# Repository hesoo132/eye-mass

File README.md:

# Eye-Mass Board  

## 🔎 Overview
**Eye-Mass** is a custom embedded hardware board designed for **real-time image processing and AI experimentation**.  
It integrates a camera (OV5640), external SDRAM, motor control, and communication interfaces to enable tasks such as **capturing and analyzing images of components inside a box**.

---

## 🔧 Hardware Features

| Component               | Purpose                                                                 |
|-------------------------|-------------------------------------------------------------------------|
| **Debug LED**           | Visual feedback for board status and firmware debugging                 |
| **SDRAM**               | Additional memory for buffering image data and running lightweight AI   |
| **OV5640 Camera**       | Captures images (e.g., counting SMD components inside a box)            |
| **Motor Driver**        | Moves the camera to capture the entire box view                         |
| **FDCAN**               | High-speed, reliable communication with external modules                |
| **USART**               | Serial interface for debugging and logging                              |
| **Temperature Sensor**  | Monitors motor driver and board ambient temperature                     |
| **Current/Voltage Monitor** | Measures system power consumption and provides protection           |

---

## 📸 Hardware Overview
| PCB Top | PCB Bottom |
|---------|------------|
|  |  |

---

## ✅ Current Status
- [x] Schematic design completed
- [x] PCB prototype (Rev. A) fabricated
- [x] SDRAM bring-up and validation
- [ ] Camera interface bring-up (OV5640)
- [x] Motor control & positioning test
- [x] Communication test (FDCAN, USART)
- [ ] Firmware integration (image capture + AI experimentation)

---

## 📑 References
- [STM32H7 Reference Manual](https://www.st.com/resource/en/reference_manual/dm00314099.pdf)  
- [OV5640 Camera Datasheet](https://www.arducam.com/downloads/datasheet/OV5640DS.pdf)

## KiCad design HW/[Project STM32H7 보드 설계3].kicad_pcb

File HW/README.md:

# Eye-Mass Hardware Design

## 🔎 Overview
The **Eye-Mass Board** is a custom embedded platform designed for **camera-based vision tasks and AI experimentation**.  
It integrates an OV5640 camera, external SDRAM, motor driver, and multiple debug/monitoring features.

---

## 📸 PCB Overview
| Top View | Bottom View |
|----------|-------------|
|  |  |

---

## 📑 Design Resources

- **Schematics**: [eye-mass.pdf](eye-mass.pdf) (PDF for quick view)
    
---

## 🔧 Key Hardware Notes
- **EDA Tool**: KiCad 9.0  
- **PCB Stackup**: 6-layer, impedance-controlled for high-speed (DCMI, FDCAN)  
- **Memory**: External SDRAM for real-time image buffering + AI workloads  
- **Camera**: OV5640 with DCMI interface for capturing and analysis  
- **Motor Driver**: Enables camera positioning to capture full target area  
- **Debugging**: LEDs + USART interface  
- **Monitoring**: Temperature and current/voltage sensing  

---

## 🧩 Schematic Highlights

### 1) MCU — STM32H723ZGT6

- **Device**: STM32H723ZGT6 
- **Connections**: Debug UART, **ST-Link Mini** (SWD), boot-mode pins, GPIO banks **PA/PB/PC/PD/PE/PF/PG**, external clock **TCXO 12 MHz**, reset circuit  
- **Purpose**: Central control with dedicated debug/boot paths and ample I/O for peripherals

### 2) SDRAM — IS42S16320F-7BL

- **Device**: IS42S16320F-7BL  
- **Interface**: **FMC** — DQ0–DQ15, A0–A12, BA0–BA1, **SDNWE/SDNCAS/SDNRAS/SDNE0/SDCKE0/SDCLK**, NBL0/NBL1  
- **Purpose**: External memory to expand capacity for image buffering and lightweight AI execution

### 3) Power

- **Key ICs**: **INA219BxD** (current/voltage monitor), **TPS562201** (buck converter)  
- **Rails**: From **+12 V** input to **+5 V / +3.3 V / +2.8 V / +1.8 V**  
- **Purpose**: Stable multi-rail supply with inline power telemetry for easier power management

### 4) Camera — OV5640

- **Sensor**: **OV5640**  
- **Interface**: **DCMI** (D0–D7, HSYNC, VSYNC, PIXCLK) + **I²C4** (SCL, SDA)  
- **Power & Control**: **+1.8 V / +2.8 V / +3.3 V** rails, LED control (**Camera_LED**, **FLASH**, **FLASH_PWM**)  
- **Use Case**: Capturing images for tasks like **counting SMD components inside a box**

### 5) FDCAN

- **Transceiver**: **MCP2562FD**  
- **Connections**: MCU **FDCAN_Tx3 / FDCAN_Rx3** ↔ bus **CANH/CANL**; includes **120 Ω** termination  
- **Purpose**: Robust CAN communication to external modules/systems

### 6) Temperature — AS6221 ×2

- **Sensors**: **AS6221** ×2  
- **Interface**: **I²C2** (SCL, SDA)  
- **Purpose**: Dual-point temperature monitoring (e.g., motor driver and board ambient)

### 7) Motor Driver — A4988

- **Driver**: **A4988**  
- **Signals**: **STEP, DIR, ENABLE, MS1, MS2, MS3**; outputs **1A/1B/2A/2B**  
- **Purpose**: Stepper control with microstepping configuration for camera positioning

### 8) microSD — SDMMC2

- **Interface**: **SDMMC2** — D0–D3, CMD, CLK, INT  
- **Purpose**: Removable storage for images and logs

---

## ✅ Progress
- [x] Schematics completed  
- [x] PCB prototype (Rev. A) fabricated  
- [x] SDRAM bring-up (partial validation ongoing)  
- [ ] Camera interface bring-up (OV5640)  
- [x] Motor driver test & positioning control  
- [x] Communication tests (FDCAN / USART)

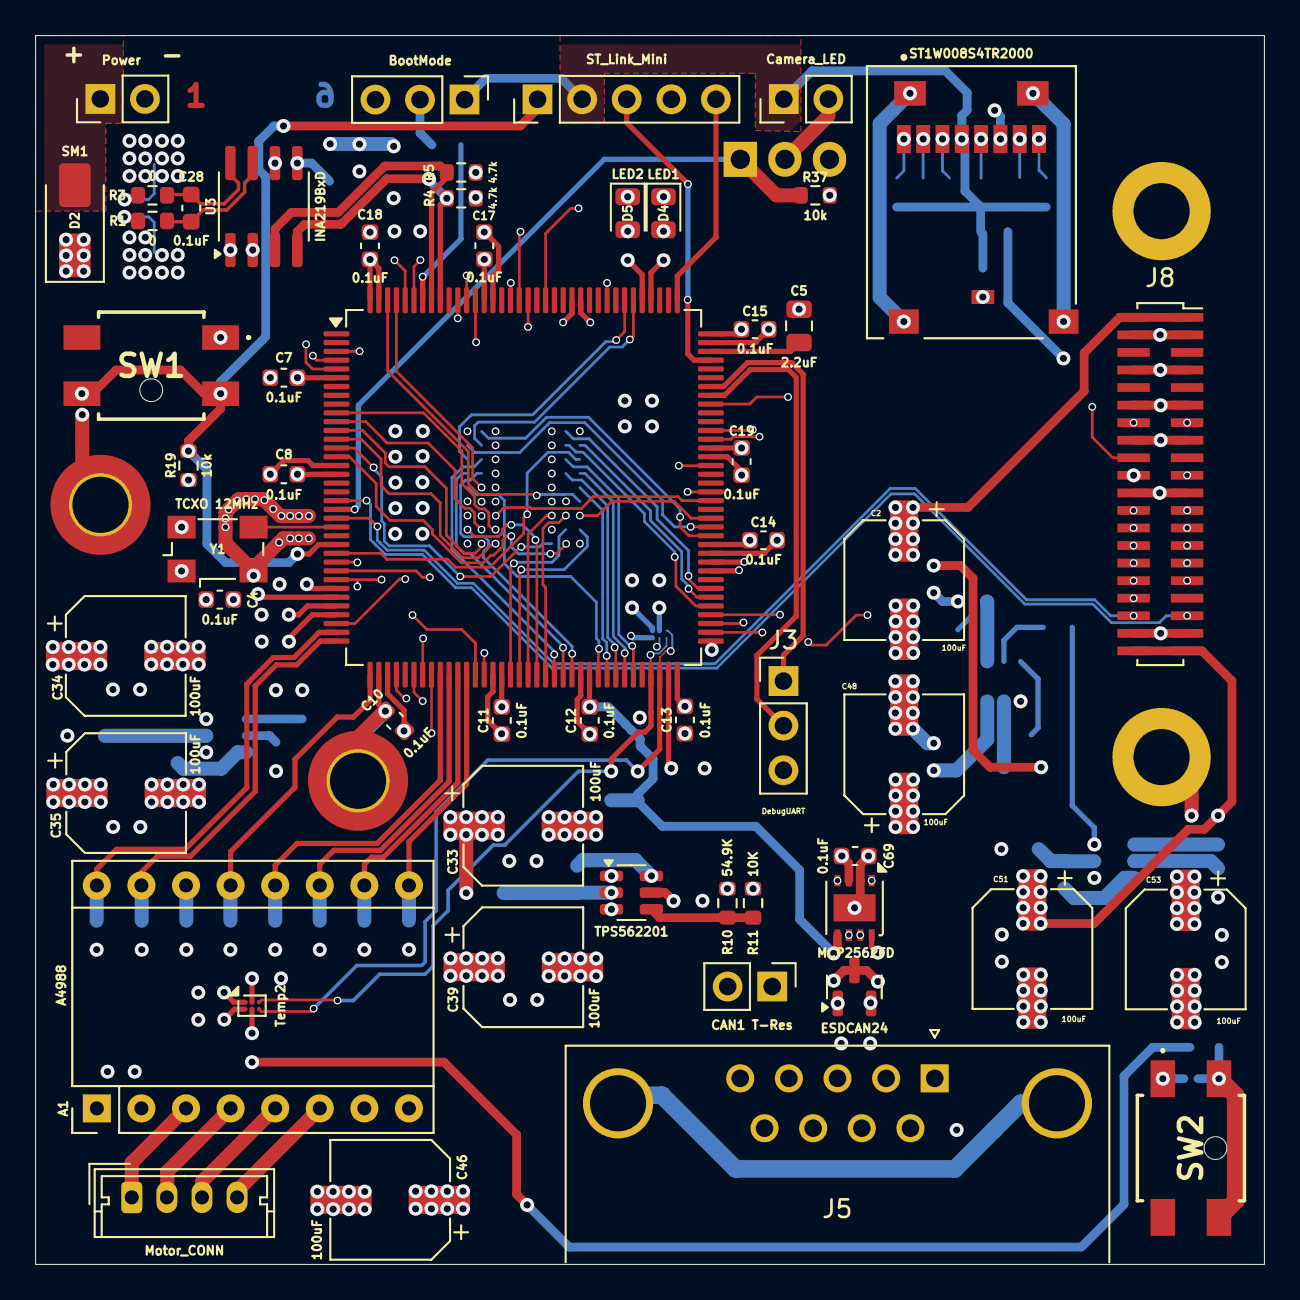
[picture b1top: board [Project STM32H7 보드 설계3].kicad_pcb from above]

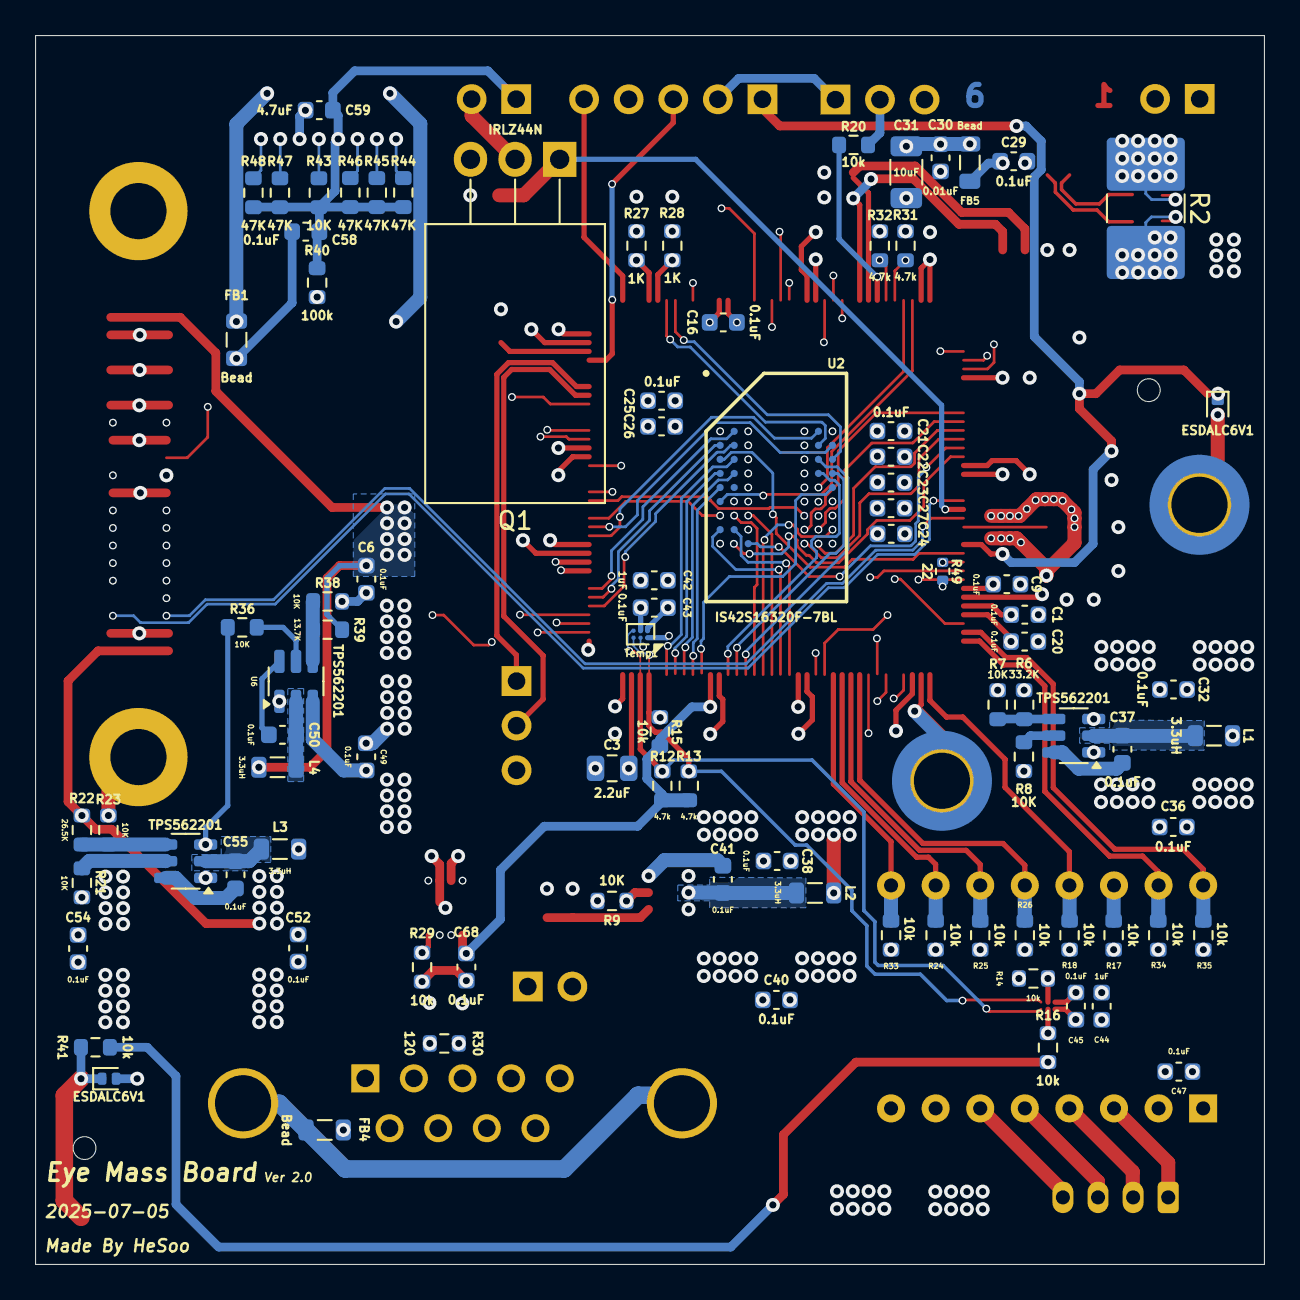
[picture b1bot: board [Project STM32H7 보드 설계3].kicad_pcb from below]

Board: 6 copper layers, 70.0 x 70.0 mm, 147 parts (90 on the bottom side), 135 nets.

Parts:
A1: A4988; Pololu_Breakout-16_15.2x20.3mm
C1, C4, C6, C7, C8, C9, C10, C11, C12, C13, C14, C15, C16, C17, C18, C19, C20, C21, C22, C23, C24, C25, C26, C27, C28, C29, C32, C36, C37, C38, C40, C41, C43, C45, C47, C49, C50, C52, C54, C55, C58, C68, C69: 0.1uF; C_0603_1608Metric
C2, C33, C34, C35, C39, C46, C48, C51, C53: 100uF; CP_Elec_6.3x5.9
C3, C5: 2.2uF; C_0805_2012Metric
C30: 0.01uF; C_0603_1608Metric
C31: 10uF; C_1206_3216Metric
C42, C44: 1uF; C_0603_1608Metric
C59: 4.7uF; C_0603_1608Metric
D1: ESDCAN24; SOT-23
D2: SM1; D_SMA
D3, D6: ESDALC6V1; D_SOD-882D
D4: LED1; LED_0805_2012Metric
D5: LED2; LED_0805_2012Metric
FB1, FB4, FB5: Bead; L_0805_2012Metric
H1, H2: MountingHole_Pad; MountingHole_3.2mm_M3_DIN965_Pad
J1: Power; PinHeader_1x02_P2.54mm_Vertical
J2: ST_Link_Mini; PinHeader_1x05_P2.54mm_Vertical
J3: DebugUART; PinHeader_1x03_P2.54mm_Vertical
J4: CAN1 T-Res; PinHeader_1x02_P2.54mm_Vertical
J5: FDCAN_1; DSUB-9_Female_Horizontal_P2.77x2.84mm_EdgePinOffset7.70mm_H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
J6: BootMode; PinHeader_1x03_P2.54mm_Vertical
J7: Camera_LED; PinHeader_1x02_P2.54mm_Vertical
J8: OV5640; PinSocket_2x20_P1.00mm_Vertical_SMD
J9: Motor_CONN; Molex_Micro-Latch_53253-0470_1x04_P2.00mm_Vertical
J10: ST1W008S4TR2000; JAE_ST1W008S4TR2000
L1, L2, L3, L4: 3.3uH; L_0805_2012Metric
Q1: IRLZ44N; TO-220-3_Horizontal_TabDown
R1, R3: 0; R_0603_1608Metric
R2: 0.1; R_2816_7142Metric
R4, R5, R12, R13, R31, R32: 4.7k; R_0603_1608Metric
R6: 33.2K; R_0603_1608Metric
R7, R8, R9, R11, R21, R23, R36, R38, R43: 10K; R_0603_1608Metric
R10: 54.9K; R_0603_1608Metric
R14, R15, R16, R17, R18, R19, R20, R24, R25, R26, R29, R33, R34, R35, R37, R41: 10k; R_0603_1608Metric
R22: 26.5K; R_0603_1608Metric
R27, R28: 1K; R_0603_1608Metric
R30: 120; R_0603_1608Metric
R39: 13.7K; R_0603_1608Metric
R40: 100k; R_0603_1608Metric
R44, R45, R46, R47, R48: 47K; R_0603_1608Metric
R49: 22; R_0402_1005Metric
SW1, SW2: RESET; TLSMDT3C020GLFS
Temp1, Temp2: AS6221; WLCSP-6_1.4x1.0mm_P0.4mm
U1: STM32H723ZGTx; LQFP-144_20x20mm_P0.5mm
U2: IS42S16320F-7BL; IS42S16320F-7BLI
U3: INA219BxD; SOIC-8_3.9x4.9mm_P1.27mm
U4, U5, U6, U8: TPS562201; SOT-23-6
U7: MCP2562FD; DFN-8-1EP_3x3mm_P0.65mm_EP1.55x2.4mm
Y1: TCXO 12MHz; Oscillator_SMD_Fox_FT5H_5.0x3.2mm

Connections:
+1V8: C2.1, C6.2, J8.1, J8.2, L4.1, R39.2
+2V8: C51.1, C52.2, J8.39, J8.40, L3.1, R22.1
+3.3V: A1.2 (VDD), C1.2, C4.1, C7.2, C8.2, C9.2, C10.2, C11.2, C12.2, C13.2, C14.2, C15.2, C16.2, C17.2, C18.2, C19.2, C20.2, C21.2, C22.2, C23.2, C24.2, C25.2, C26.2, C27.2, C30.1, C31.1, C32.2, C34.1, C42.1, C43.1, C44.1, C45.1, C47.1, C58.2, C59.2, C68.1, FB5.2, J2.2, J6.1, J7.1, J10.C4 (VDD), L1.1, R4.1, R5.1, R6.2, R12.1, R13.1, R14.1, R15.1, R16.1, R17.1, R18.2, R19.1, R24.2, R25.2, R26.2, R31.1, R32.1, R34.2, R35.2, R40.1, R41.1, R43.1, R44.1, R45.1, R46.1, R47.1, R48.1, Temp1.A2 (VDD), Temp2.A2 (VDD), U1.6 (VBAT), U1.17 (VDD), U1.30 (VDD), U1.32 (VREF+), U1.33 (VDDA), U1.39 (VDD), U1.52 (VDD), U1.62 (VDD), U1.72 (VDD), U1.84 (VDD), U1.95 (VDD33USB), U1.108 (VDD), U1.121 (VDD), U1.131 (VDD), U1.143 (PDR_ON), U1.144 (VDD), U2.A7 (VDDQ_1), U2.A9 (VDD_1), U2.B3 (VDDQ_2), U2.C7 (VDDQ_3), U2.D3 (VDDQ_4), U2.E7 (VDD_2), U2.J9 (VDD_3), U7.5 (Vio), Y1.1 (VC), Y1.4 (VDD)
+5V: C33.1, C38.2, C69.1, L2.2, R10.2, U7.3 (VDD)
+12V: A1.8 (VMOT), C35.1, C36.2, C39.1, C40.2, C46.1, C48.1, C49.2, C53.1, C54.2, R1.2, R2.1, R8.2, R9.2, R21.2, R36.2, U4.3 (VIN), U5.3 (VIN), U6.3 (VIN), U8.3 (VIN)
/FDCAN/CAN1_N: D1.1 (A1), J4.1, J5.7, U7.6 (CANL)
/FDCAN/CAN1_P: D1.2 (A2), J5.2, R30.2, U7.7 (CANH)
/POWER/S_N: C28.1, R1.1, U3.7 (IN-)
/POWER/S_P: C28.2, R3.2, U3.8 (IN+)
/SDCARD/SD_SDMMC_CLK: J10.C5 (CLK), R43.2, R49.2
AS6221_I2C2_SCL: R13.2, Temp1.C1 (SCL), Temp2.C1 (SCL), U1.69 (PB10)
AS6221_I2C2_SDA: R12.2, Temp1.C2 (SDA), Temp2.C2 (SDA), U1.70 (PB11)
BAT_SCL1: R4.2, U1.136 (PB6), U3.4 (SCL)
BAT_SDA1: R5.2, U1.137 (PB7), U3.3 (SDA)
BOOT0: R20.2, U1.138 (BOOT0)
Camera_Reset: J8.18, U1.128 (PG13)
DCMI_D0: J8.24, U1.96 (PC6)
DCMI_D1: J8.23, U1.97 (PC7)
DCMI_D2: J8.26, U1.74 (PB13)
DCMI_D3: J8.25, U1.126 (PG11)
DCMI_D4: J8.28, U1.3 (PE4)
DCMI_D5: J8.27, U1.117 (PD3)
DCMI_D6: J8.30, U1.4 (PE5)
DCMI_D7: J8.29, U1.5 (PE6)
DCMI_HSYNC: J8.32, U1.40 (PA4)
DCMI_PIXCLK: J8.34, U1.42 (PA6)
DCMI_VSYNC: J8.31, U1.124 (PG9)
DIR: A1.16 (DIR), R35.1, U1.35 (PA1)
ENABLE: A1.9 (~ENABLE), R33.1, U1.48 (PB2)
FDCAN_Rx3: U1.81 (PD12), U7.4 (RXD)
FDCAN_SHDN3: R29.1, U1.44 (PC4), U7.8 (SHDN)
FDCAN_Tx3: U1.82 (PD13), U7.1 (TXD)
FLASH: J8.35, U1.20 (PF8)
FLASH_PWM: Q1.1 (G), R37.1, U1.21 (PF9)
FMC_A0: U1.10 (PF0), U2.H7 (A0)
FMC_A1: U1.11 (PF1), U2.H8 (A1)
FMC_A2: U1.12 (PF2), U2.J8 (A2)
FMC_A3: U1.13 (PF3), U2.J7 (A3)
FMC_A4: U1.14 (PF4), U2.J3 (A4)
FMC_A5: U1.15 (PF5), U2.J2 (A5)
FMC_A6: U1.50 (PF12), U2.H3 (A6)
FMC_A7: U1.53 (PF13), U2.H2 (A7)
FMC_A8: U1.54 (PF14), U2.H1 (A8)
FMC_A9: U1.55 (PF15), U2.G3 (A9)
FMC_A10: U1.56 (PG0), U2.H9 (A10)
FMC_A11: U1.57 (PG1), U2.G2 (A11)
FMC_A12: U1.87 (PG2), U2.G1 (A12)
FMC_BA0: U1.89 (PG4), U2.G7 (BA0)
FMC_BA1: U1.90 (PG5), U2.G8 (BA1)
FMC_D0: U1.85 (PD14), U2.A8 (DQ0)
FMC_D1: U1.86 (PD15), U2.B9 (DQ1)
FMC_D2: U1.114 (PD0), U2.B8 (DQ2)
FMC_D3: U1.115 (PD1), U2.C9 (DQ3)
FMC_D4: U1.58 (PE7), U2.C8 (DQ4)
FMC_D5: U1.59 (PE8), U2.D9 (DQ5)
FMC_D6: U1.60 (PE9), U2.D8 (DQ6)
FMC_D7: U1.63 (PE10), U2.E9 (DQ7)
FMC_D8: U1.64 (PE11), U2.E1 (DQ8)
FMC_D9: U1.65 (PE12), U2.D2 (DQ9)
FMC_D10: U1.66 (PE13), U2.D1 (DQ10)
FMC_D11: U1.67 (PE14), U2.C2 (DQ11)
FMC_D12: U1.26 (PC0), U2.C1 (DQ12)
FMC_D13: U1.77 (PD8), U2.B2 (DQ13)
FMC_D14: U1.78 (PD9), U2.B1 (DQ14)
FMC_D15: U1.79 (PD10), U2.A2 (DQ15)
FMC_NBL0: U1.141 (PE0), U2.E8 (DQML)
FMC_NBL1: U1.142 (PE1), U2.F1 (DQMH)
FMC_SDCKE0: U1.29 (PC3_C), U2.F3 (CKE)
FMC_SDCLK: U1.93 (PG8), U2.F2 (CLK)
FMC_SDNCAS: U1.132 (PG15), U2.F7 (~CAS)
FMC_SDNE0: U1.28 (PC2_C), U2.G9 (~CS)
FMC_SDNRAS: U1.49 (PF11), U2.F8 (~RAS)
FMC_SDNWE: U1.43 (PA7), U2.F9 (~WE)
GND: A1.1 (GND), A1.7 (GND), C1.1, C2.2, C3.1, C4.2, C5.1, C6.1, C7.1, C8.1, C9.1, C10.1, C11.1, C12.1, C13.1, C14.1, C15.1, C16.1, C17.1, C18.1, C19.1, C20.1, C21.1, C22.1, C23.1, C24.1, C25.1, C26.1, C27.1, C29.2, C30.2, C31.2, C32.1, C33.2, C34.2, C35.2, C36.1, C38.1, C39.2, C40.1, C42.2, C43.2, C44.2, C45.2, C46.2, C47.2, C48.2, C49.1, C51.2, C52.1, C53.2, C54.1, C58.1, C59.1, C68.2, C69.2, D1.3 (common), D3.2 (A), D4.1 (K), D5.1 (K), D6.2 (A), FB1.2, FB4.2, H1.1, H2.1, J1.2, J2.4, J3.3, J5.3, J5.5, J5.6, J6.3, J8.3, J8.4, J8.7, J8.8, J8.11, J8.12, J8.15, J8.16, J8.20, J8.21, J8.22, J8.37, J8.38, J10.C6 (VSS), Q1.3 (S), R7.2, R11.2, R23.2, R29.2, R33.2, R37.2, R38.2, SW1.1 (B), SW2.1 (B), Temp1.A1 (VSS), Temp1.B2 (ADD0), Temp2.A1 (VSS), U1.16 (VSS), U1.31 (VSSA), U1.38 (VSS), U1.51 (VSS), U1.61 (VSS), U1.83 (VSS), U1.94 (VSS), U1.107 (VSS), U1.120 (VSS), U1.130 (VSS), U2.A1 (VSS_1), U2.A3 (VSSQ_1), U2.B7 (VSSQ_2), U2.C3 (VSSQ_3), U2.D7 (VSSQ_4), U2.E3 (VSS_2), U2.J1 (VSS_3), U3.1 (A1), U3.2 (A0), U3.6 (GND), U4.1 (GND), U5.1 (GND), U6.1 (GND), U7.2 (VSS), U7.9 (PAD), U8.1 (GND), Y1.2 (GND)
I2C4_SCL: J8.14, R32.2, U1.139 (PB8)
I2C4_SDA: J8.13, R31.2, U1.140 (PB9)
MS1: A1.10 (MS1), R24.1, U1.47 (PB1)
MS2: A1.11 (MS2), R25.1, U1.46 (PB0)
MS3: A1.12 (MS3), R26.1, U1.45 (PC5)
Motor1: A1.3 (1B), J9.1
Motor2: A1.4 (1A), J9.2
Motor3: A1.5 (2A), J9.3
Motor4: A1.6 (2B), J9.4
Motor_Reset: A1.13 (~RESET), R18.1, U1.37 (PA3)
unnamed: A1.14 (~SLEEP), R17.2
unnamed: C3.2, U1.71 (VCAP)
unnamed: C5.2, U1.106 (VCAP)
unnamed: D2.2 (A), J1.1
unnamed: D2.1 (K), R2.2, R3.1
unnamed: D4.2 (A), R27.2
unnamed: D5.2 (A), R28.2
unnamed: FB1.1, J10.GND1 (SHIELD), J10.GND2 (SHIELD), J10.GND3 (SHIELD), J10.GND4 (SHIELD)
unnamed: J4.2, R30.1
unnamed: FB4.1, J5.0 (PAD)
unnamed: J6.2, R20.1
unnamed: J7.2, Q1.2 (D)
unnamed: R15.2, Temp1.B1 (Alert/ADD1)
unnamed: R16.2, Temp2.B2 (ADD0)
unnamed: R14.2, Temp2.B1 (Alert/ADD1)
unnamed: R27.1, U1.112 (PC11)
unnamed: R28.1, U1.113 (PC12)
unnamed: U1.23 (PH0), Y1.3 (OUT)
unnamed: C29.1, FB5.1, U3.5 (VS)
unnamed: R9.1, U4.5 (EN)
unnamed: C41.2, L2.1, U4.2 (SW)
unnamed: C41.1, U4.6 (VBST)
unnamed: R10.1, R11.1, U4.4 (VFB)
unnamed: R8.1, U5.5 (EN)
unnamed: C37.2, L1.2, U5.2 (SW)
unnamed: C37.1, U5.6 (VBST)
unnamed: R6.1, R7.1, U5.4 (VFB)
unnamed: R36.1, U6.5 (EN)
unnamed: C50.2, L4.2, U6.2 (SW)
unnamed: C50.1, U6.6 (VBST)
unnamed: R38.1, R39.1, U6.4 (VFB)
unnamed: R21.1, U8.5 (EN)
unnamed: C55.2, L3.2, U8.2 (SW)
unnamed: C55.1, U8.6 (VBST)
unnamed: R22.2, R23.1, U8.4 (VFB)
RCC_MCO_1: J8.19, U1.100 (PA8)
SD_SDMMC2_CLK: R49.1, U1.27 (PC1)
SD_SDMMC2_CMD: J10.C3 (CMD), R46.2, U1.34 (PA0)
SD_SDMMC2_D0: J10.C7 (DAT0), R47.2, U1.75 (PB14)
SD_SDMMC2_D1: J10.C8 (DAT1), R48.2, U1.76 (PB15)
SD_SDMMC2_D2: J10.C1 (DAT2), R44.2, U1.133 (PB3(JTDO)
SD_SDMMC2_D3: J10.C2 (DAT3/CD), R45.2, U1.127 (PG12)
SD_SDMMC2_INT: J10.SW (DET), R40.2, U1.134 (PB4(NJTRST))
SHUTTER: J8.36, U1.22 (PF10)
STEP: A1.15 (STEP), R34.1, U1.36 (PA2)
ST_Link_Reset: D3.1 (K), J2.1, R19.2, SW1.2 (C), U1.25 (NRST)
ST_Link_SWCLK: J2.5, U1.109 (PA14(JTCK)
ST_Link_SWDIO: J2.3, U1.105 (PA13(JTMS)
TestButton: D6.1 (K), R41.2, SW2.2 (C), U1.73 (PB12)
USART1_RX: J3.1, U1.102 (PA10)
USART1_TX: J3.2, U1.101 (PA9)

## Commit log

2025-08-21 Eye-mass Hardware v2.0
2025-08-22 file update
